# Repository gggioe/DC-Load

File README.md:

Work in progress. At this point, no fully functional board has been produced. Some functional blocks or components have been tested with good results, but since this is a hobby project, there is no ETA. Software and Hardware (even this repo) will be constantly updated. I plan to release a fully functional prototype as soon as possible.

# The Idea
The idea is to build a fully functional instrument that can be easily compared to commercial ones. Commercially available loads are precise, some of them are software-controlled and come with a warranty, however, they tend to not have a high performance/price ratio. Some cheap 30-50 euros Chinese designs are just bad, with very limited specs (generally under 50V, 5A, 100W), and also they tend to use fake or extremely cheap components that fail even at the advertised specs. "Hobbyist" good quality  400 euros loads come with limited specifications like 150V, 20A, and 200W max power. This is ok for general-purpose power supply tests however, nowadays battery tends to have high discharge rates so if you want to test your e-bike battery pack for example, more expensive loads capable of 60-100A, 3-4 kW should be used. Those types of loads however tend to have very high prices>2k and in some cases, you have to be a company to know the exact price. Online exist various more or less good DIY attempts, however, some are a complete joke with specs like 2A, 20V, and 40W max. Don't get me wrong, 20V 2A is perfectly fine for low-power IOT stuff for example, however, nowadays devices tend to get more and more power hungry and power supply more powerful, with a 40w limit even a modern type c phone charger is impossible to fully test. More complex ones are not as precise as i hoped or maybe do not come with an interface that makes it a real bench instrument. Overall all of these projects gave me the impression of being a little "incomplete" and i had a feeling that no one really attempted a commercially competitive DIY solution. At this point, the only thing to do is to build my own DC electronic load that can be used as a real instrument and hopefully be a decent competitor of some commercial solutions, how hard can it be?... right?...

# General design specifications
The main goals are: 

-Good precision: Precise components are cheap these days so since in most cases they outperform more complex discrete designs both in specs and dimension, i will use them without complaining. In general, around 10mA accuracy should be ok for a high power load and for the average hobbyist like me. 

-Good stability: the system should not spontaneously oscillate for example when a too-high/low current is set. Aggressive transient or step can be quite challenging, even if the simulation shows good results, parasitic inductance/capacitance of the real world in components/wiring/trace can cause some instability. What makes the situation worse is that real-world instability/noise can be quite challenging to reproduce in simulation so for now since i do not have the right equipment, i will trust the simulation.

-Safety: The load should remain relatively safe in case of catastrophic failures like reverse polarity or input overvoltage. Due to the moderate-high voltage (maybe up to 500v in later design). Isolation is also a key factor, if an earthed, relatively high voltage source is connected, the user interface like display, button, encoder, pc, etc. should remain isolated. When browsing the internet i noticed that a common flaw that both commercial and non-commercial loads share is the lack of a proper DC-rated transistor, common design even in the 3/400 euro price point tends to use IRF260N (or similar) mosfet, however, if you take a look at the datasheet (safe operating area) they are not even DC rated, this means that DC operation (which is the average operation) is not safe for them. Companies generally compensate by massively underloading them but for me, it is just a bad design. Maybe those transistors were independently tested however in my design i want to use only properly manufactured DC-rated components.

-Modularity: If not too difficult, a modular design is well accepted since it allows to have multiple configurations. Due to the tight demands, if a module ends up being expensive the user who may not need too high specs can build a lower-cost unit and later if necessary add modules to expand the power capability. Of course, if multiple modules in parallel are connected the overall accuracy is reduced because the overall error will be the sum of the error of each module.

-Competitive specs: If i will be not able to achieve at least the same specifications as commercial products there is no point continuing to develop this project since in that case, a worse product will cost me around the same as a commercial well-established one. A good starting point for me is to at least match the commercial product specs so: ≥150V, ≥200W, and since the modular design ≥20A per module should be fine.

-Price: Obviously the cost should remain as low as possible, however, due to my demands an acceptable price will be <100 euros per module. In that case, a complete unit with similar (or even better) specs of commercial loads will end up costing less than the commercial solution.

# Power and Thermal considerations
At now on mouser the best mosfet regarding quality/price ratio is the FDP61N20 however higher power (and more expensive) mosfet such as FDH45N50 can be used, later in the design i will mark some good mid-range alternatives. Due to the relatively small mosfet surface area, in order to get the best performance liquid metal and water cooling system should be used in order to get the best performance. The overall dissipated power strictly depends on the used mosfet, by using a relatively large package transistor with 40x80 water block, liquid metal, and adequate size radiator/pump, 1kW or more (in case of multiple modules in parallel) should be possible. As intuition, heat is the critical part of this project, mosfet has a temperature derating curve that should not be excedeed for safe DC operation, even if a mosfet is 450W max rated for example this will not be true at 50 degree case temperature. Due to the junction-case thermal resistance if the derating curve is not respected even with a relatively low case temperature of around 50 degrees the die will exceed the 150 degree limit thus destroying the transistor. To make things worse each thermal "layer" such as thermal paste, radiator, etc. has its own thermal resistance that adds up to the total mosfet-ambient thermal resistance. At this point i perform some thermal estimation, however, it does not make much sense to upload these numbers since these are just guesses, because to my surprise even large radiator/thermal paste manufacturers do not share the thermal property of their product such as thermal resistance, airflow graph, etc. At this point is unclear to me how without the exact manufacture number the end user should implement a product. It seems like even the pc builder community does not have a clear answer to my problem, and i really don't trust any rule of thumb (like the 120mm x 100W). Now, even if i already know that this is not possible, the only thing that i can do is to experimentally validate each solution starting from the "best", in reality since this will cost me way too much money and time i think that i will use one 80x40 copper (or nickel-plated) water block + Galinstan based thermal compound and then add 120x240 or 120x360mm radiator until i reach decent temperatures.

# Simulation and Waveform
Module Schematic:

1mA Pulsed test:

Even with slightly worse performing op-amps, 1mA is theoretically possible

20A Pulsed test:

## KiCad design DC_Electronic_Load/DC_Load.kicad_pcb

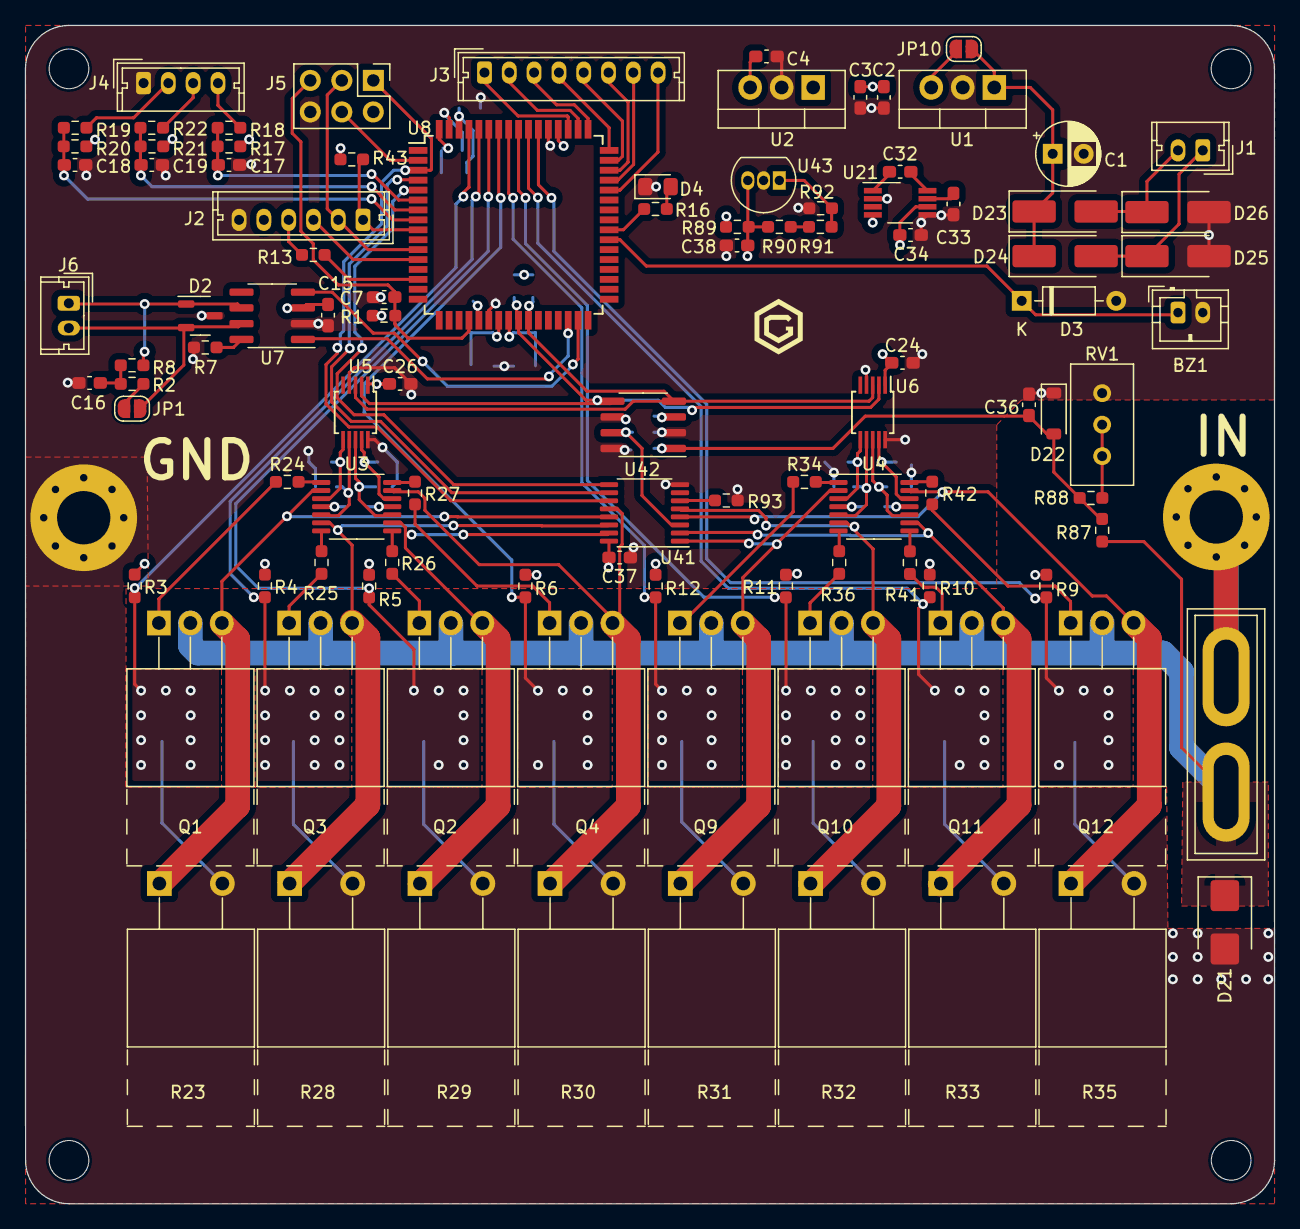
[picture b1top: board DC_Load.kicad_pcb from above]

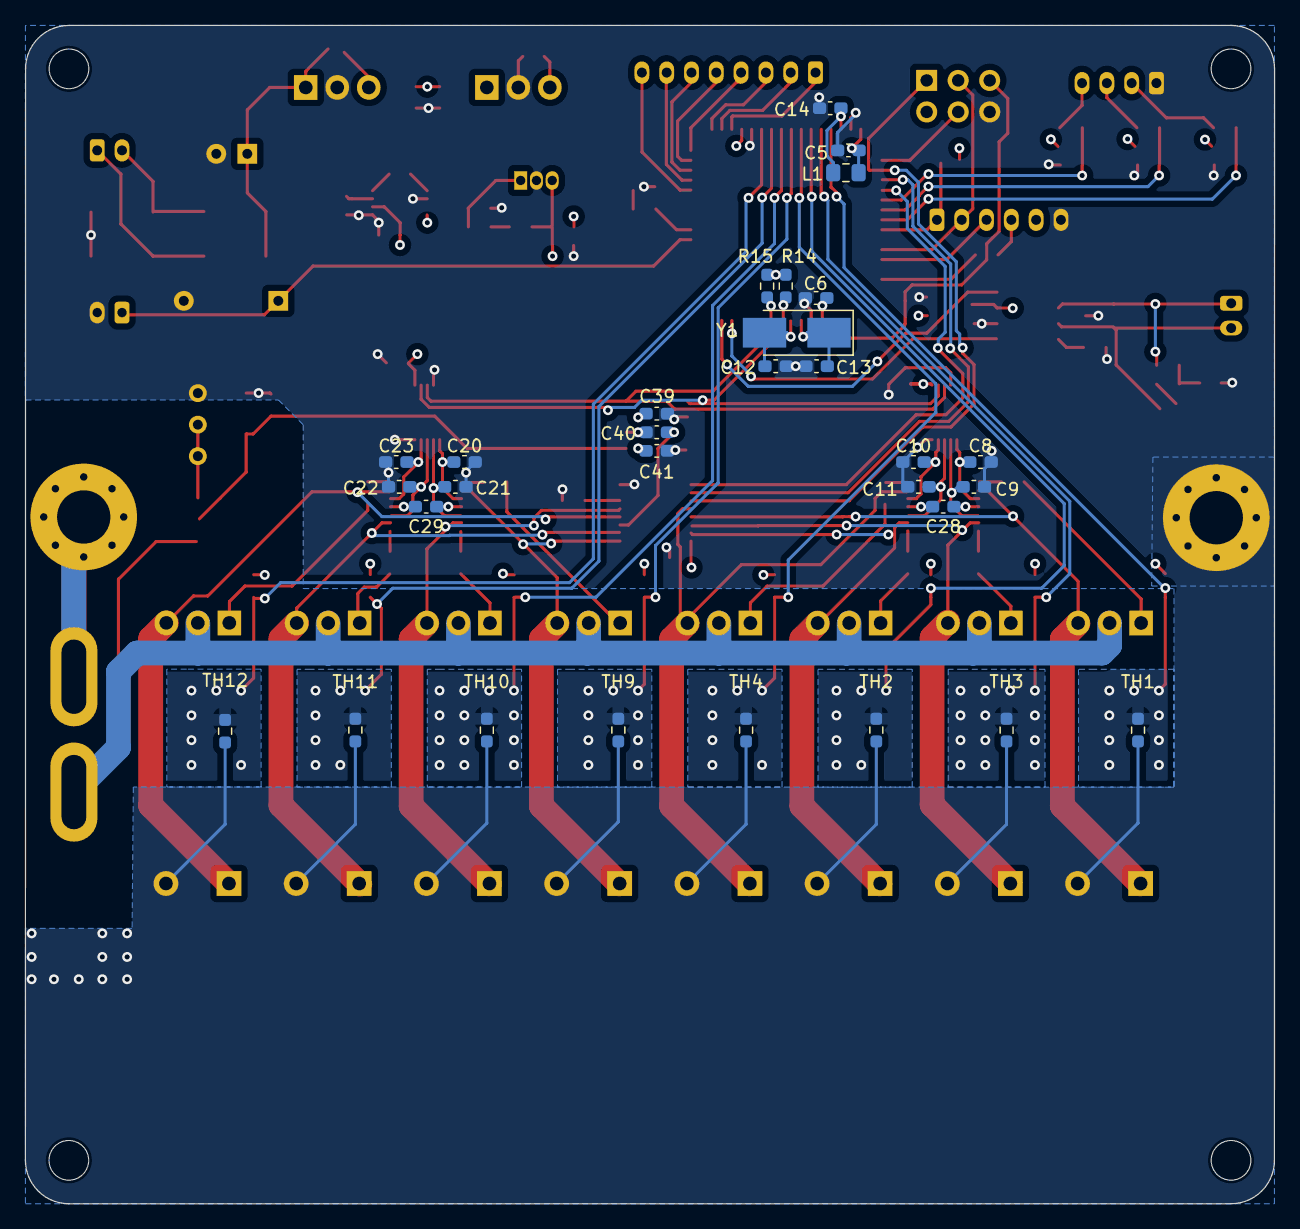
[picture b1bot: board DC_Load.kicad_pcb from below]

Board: 4 copper layers, 100.7 x 95.0 mm, 139 parts (30 on the bottom side), 98 nets.

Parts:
BZ1: Buzzer; JST_PH_B2B-PH-K_1x02_P2.00mm_Vertical
C1: 1000u; CP_Radial_D5.0mm_P2.50mm
C2, C4: 1u; C_0603_1608Metric_Pad1.08x0.95mm_HandSolder
C3, C5, C6, C7, C8, C9, C10, C11, C14, C15, C16, C17, C18, C19, C20, C21, C22, C23, C24, C26, C28, C29, C37, C38, C39: 100n; C_0603_1608Metric_Pad1.08x0.95mm_HandSolder
C12, C13, C36: 22p; C_0603_1608Metric_Pad1.08x0.95mm_HandSolder
C32: 5u; C_0603_1608Metric_Pad1.08x0.95mm_HandSolder
C33, C34: 22u; C_0603_1608Metric_Pad1.08x0.95mm_HandSolder
C40, C41: 1n; C_0603_1608Metric_Pad1.08x0.95mm_HandSolder
D2: PESD2CAN; SOT-23-3
D3: 1N4148; D_DO-35_SOD27_P7.62mm_Horizontal
D4: LED; LED_0805_2012Metric_Pad1.15x1.40mm_HandSolder
D21: SM6T200A; D_SMB
D22: 4.5V; D_SOD-123
D23, D24, D25, D26: SS14; D_SMA_Handsoldering
F1: 50A; Fuse_Blade_ATO_directSolder
H1: PWR+; MountingHole_4.3mm_M4_Pad_Via
H2: PWR-; MountingHole_4.3mm_M4_Pad_Via
H3, H4, H5, H6: MountingHole; MountingHole_3.2mm_M3
J1, J6: Conn_01x02_Pin; Molex_Micro-Latch_53253-0270_1x02_P2.00mm_Vertical
J2: Conn_01x06_Pin; Molex_Micro-Latch_53253-0670_1x06_P2.00mm_Vertical
J3: Conn_01x08_Pin; Molex_Micro-Latch_53253-0870_1x08_P2.00mm_Vertical
J4: Conn_01x04_Pin; Molex_Micro-Latch_53253-0470_1x04_P2.00mm_Vertical
J5: Conn_02x03_Odd_Even; PinHeader_2x03_P2.54mm_Vertical
JP1, JP10: Jumper_2_Open; SolderJumper-2_P1.3mm_Open_RoundedPad1.0x1.5mm
L1: 10uH; L_0805_2012Metric_Pad1.15x1.40mm_HandSolder
Q1, Q2, Q3, Q4, Q9, Q10, Q11, Q12: FDP61N20; TO-220-3_Horizontal_TabUp
R1, R3, R4, R5, R6, R9, R10, R11, R12, R14, R15, R43, R92: 10k; R_0603_1608Metric_Pad0.98x0.95mm_HandSolder
R2, R8, R89: 56; R_0603_1608Metric_Pad0.98x0.95mm_HandSolder
R7, R17, R20, R21: 47k; R_0603_1608Metric_Pad0.98x0.95mm_HandSolder
R13: 220; R_0603_1608Metric_Pad0.98x0.95mm_HandSolder
R16: 330; R_0603_1608Metric_Pad0.98x0.95mm_HandSolder
R18, R19, R22, R93: 1k; R_0603_1608Metric_Pad0.98x0.95mm_HandSolder
R23, R28, R29, R30, R31, R32, R33, R35: 1R; TO-220-2_Horizontal_TabUp
R24, R25, R26, R27, R34, R36, R41, R42: 1.2k; R_0603_1608Metric_Pad0.98x0.95mm_HandSolder
R87: 1M; R_0603_1608Metric_Pad0.98x0.95mm_HandSolder
R88: 22k; R_0603_1608Metric_Pad0.98x0.95mm_HandSolder
R90, R91: 3.6k; R_0603_1608Metric_Pad0.98x0.95mm_HandSolder
RV1: 1k; Potentiometer_Bourns_3296W_Vertical
TH1, TH2, TH3, TH4, TH9, TH10, TH11, TH12: 10k; R_0603_1608Metric_Pad0.98x0.95mm_HandSolder
U1: L7812; TO-220-3_Vertical
U2: L7805; TO-220-3_Vertical
U3, U4: NCS21914; TSSOP-14_4.4x5mm_P0.65mm
U5, U6: MCP4728; MSOP-10_3x3mm_P0.5mm
U7: MCP2551-I-SN; SOIC-8_3.9x4.9mm_P1.27mm
U8: AT90CAN64-16A; TQFP-64_14x14mm_P0.8mm
U9: Gio_5x5
U21: LM7705; VSSOP-8_3.0x3.0mm_P0.65mm
U41: XS3A4051PWJ; TSSOP-16_4.4x5mm_P0.65mm
U42: MCP3422; SOIC-8_3.9x4.9mm_P1.27mm
U43: TL431LP; TO-92_Inline
Y1: Crystal; Crystal_SMD_5032-2Pin_5.0x3.2mm_HandSoldering

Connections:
+4V: C37.1, C38.1, R89.2, R90.1, U41.16 (VCC), U43.3 (K)
+5V: C4.1, C6.1, C14.1, C15.1, C24.1, C26.1, C39.1, J2.5, J5.2, L1.1, R1.1, R3.1, R4.1, R5.1, R6.1, R9.1, R10.1, R11.1, R12.1, R14.1, R15.2, R17.1, R20.1, R21.1, R43.2, R89.1, U2.3 (OUT), U5.1 (VDD), U6.1 (VDD), U7.3 (VDD), U8.21 (VCC), U8.52 (VCC), U8.62 (AREF), U21.4 (VDD), U42.3 (Vdd)
+12V: C2.1, C3.1, C28.1, C29.1, JP10.2 (B), U1.3 (OUT), U2.1 (IN), U3.4 (V+), U4.4 (V+)
-VSW: C28.2, C29.2, C34.1, U3.11 (V-), U4.11 (V-), U21.6 (VOUT)
B1: J5.1, U8.3 (PE1), U41.11 (S1)
B2: U8.4 (PE2), U41.10 (S2)
B3: U8.5 (PE3), U41.9 (S3)
BCKL_CTRL: R13.2, U8.14 (PB4)
BZ: BZ1.1 (-), D3.1 (K), U8.39 (PC4)
C1: J3.5, U8.47 (PA4)
C2: J3.6, U8.46 (PA5)
C3: J3.7, U8.45 (PA6)
C4: J3.8, U8.44 (PA7)
CAN_RX: U7.4 (RXD), U8.31 (PD6)
CAN_TX: U7.1 (TXD), U8.30 (PD5)
CH1: C8.1, U3.3 (+), U5.6 (VOUTA)
CH2: C9.1, U3.5 (+), U5.7 (VOUTB)
CH3: C11.1, U3.10 (+), U5.8 (VOUTC)
CH4: C10.1, U3.12 (+), U5.9 (VOUTD)
CH5: C20.1, U4.3 (+), U6.6 (VOUTA)
CH6: C21.1, U4.5 (+), U6.7 (VOUTB)
CH7: C22.1, U4.10 (+), U6.8 (VOUTC)
CH8: C23.1, U4.12 (+), U6.9 (VOUTD)
CS: J2.1, R43.1, U8.9 (PE7)
E: J5.4, U8.2 (PE0)
EN1: C17.1, R17.2, R18.1, U8.6 (PE4)
EN2: C19.1, R21.2, R22.1, U8.7 (PE5)
GND: BZ1.2 (+), C1.2, C2.2, C3.2, C4.2, C5.2, C6.2, C7.2, C8.2, C9.2, C10.2, C11.2, C12.2, C13.2, C14.2, C15.2, C16.2, C17.2, C18.2, C19.2, C20.2, C21.2, C22.2, C23.2, C24.2, C26.2, C33.2, C34.2, C36.2, C37.2, C38.2, C39.2, C40.2, C41.2, D2.3 (common), D3.2 (A), D4.1 (K), D21.2 (A2), D22.1 (A1), D25.2 (A), D26.2 (A), H2.1, J2.6, J4.1, J5.6, R7.1, R23.2, R28.2, R29.2, R30.2, R31.2, R32.2, R33.2, R35.2, R92.2, R93.1, RV1.3, TH1.2, TH2.2, TH3.2, TH4.2, TH9.2, TH10.2, TH11.2, TH12.2, U1.2 (GND), U2.2 (GND), U5.4 (~LDAC), U5.10 (VSS), U6.4 (~LDAC), U6.10 (VSS), U7.2 (VSS), U8.22 (GND), U8.53 (GND), U8.63 (AGND), U21.2 (GND), U21.5 (GND), U41.8 (GND), U42.2 (CH1-), U42.6 (Vss), U42.8 (CH2-), U43.2 (A)
I1: Q1.3 (S), R23.1, U3.2 (-), U41.13 (Y0)
I2: Q3.3 (S), R28.1, U3.6 (-), U41.14 (Y1)
I3: Q2.3 (S), R29.1, U3.9 (-), U41.15 (Y2)
I4: Q4.3 (S), R30.1, U3.13 (-), U41.12 (Y3)
I5: Q9.3 (S), R31.1, U4.2 (-), U41.1 (Y4)
I6: Q10.3 (S), R32.1, U4.6 (-), U41.5 (Y5)
I7: Q11.3 (S), R33.1, U4.9 (-), U41.2 (Y6)
I8: Q12.3 (S), R35.1, U4.13 (-), U41.4 (Y7)
IMP: C40.1, U41.3 (Z), U42.7 (CH2+)
IN: D21.1 (A1), F1.1, Q1.2 (D), Q2.2 (D), Q3.2 (D), Q4.2 (D), Q9.2 (D), Q10.2 (D), Q11.2 (D), Q12.2 (D), R87.2
MOSI: J2.3, U8.12 (PB2)
unnamed: C16.1, R2.1, R8.2
unnamed: D2.1 (A1), J6.1, R8.1, U7.6 (CANL)
unnamed: D2.2 (A2), J6.2, JP1.1 (A), U7.7 (CANH)
unnamed: D4.2 (A), R16.2
unnamed: D23.2 (A), D26.1 (K), J1.2
unnamed: D24.2 (A), D25.1 (K), J1.1
unnamed: F1.2, H1.1
unnamed: J2.4, R13.1
unnamed: J4.2, R19.2
unnamed: J4.3, R22.2
unnamed: J4.4, R18.2
unnamed: JP1.2 (B), R2.2
unnamed: Q1.1 (G), R24.2
unnamed: Q2.1 (G), R26.2
unnamed: Q3.1 (G), R25.2
unnamed: Q4.1 (G), R27.2
unnamed: Q9.1 (G), R34.2
unnamed: Q10.1 (G), R36.2
unnamed: Q11.1 (G), R41.2
unnamed: Q12.1 (G), R42.2
unnamed: R24.1, U3.1
unnamed: R25.1, U3.7
unnamed: R26.1, U3.8
unnamed: R27.1, U3.14
unnamed: R34.1, U4.1
unnamed: R36.1, U4.7
unnamed: R41.1, U4.8
unnamed: R42.1, U4.14
unnamed: R88.2, RV1.1, RV1.2
unnamed: R90.2, R91.1
unnamed: R7.2, U7.8 (Rs)
unnamed: C5.1, L1.2, U8.64 (AVCC)
unnamed: C12.1, U8.24 (XTAL1), Y1.2
unnamed: C13.1, U8.23 (XTAL2), Y1.1
unnamed: C32.1, U21.1 (CF+)
unnamed: C32.2, U21.8 (CF-)
unnamed: C33.1, U21.7 (CRES)
unnamed: R93.2, U41.6 (E)
unnamed: R91.2, R92.1, U43.1 (REF)
OUT_ON: R16.1, U8.40 (PC5)
R1: J3.1, U8.51 (PA0)
R2: J3.2, U8.50 (PA1)
R3: J3.3, U8.49 (PA2)
R4: J3.4, U8.48 (PA3)
RST: C7.1, J5.5, R1.2, U8.20 (~RESET)
SCK: J2.2, J5.3, U8.11 (PB1)
SCL: R14.2, U5.2 (SCL), U6.2 (SCL), U8.25 (PD0), U42.5 (SCL)
SDA: R15.1, U5.3 (SDA), U6.3 (SDA), U8.26 (PD1), U42.4 (SDA)
SW: C18.1, R19.1, R20.2, U8.8 (PE6)
TM1: R3.2, TH1.1, U8.61 (PF0)
TM2: R4.2, TH3.1, U8.60 (PF1)
TM3: R5.2, TH2.1, U8.59 (PF2)
TM4: R6.2, TH4.1, U8.58 (PF3)
TM5: R12.2, TH9.1, U8.57 (PF4)
TM6: R11.2, TH10.1, U8.56 (PF5)
TM7: R10.2, TH11.1, U8.55 (PF6)
TM8: R9.2, TH12.1, U8.54 (PF7)
VCC: C1.1, D23.1 (K), D24.1 (K), JP10.1 (A), U1.1 (IN)
VMP: C36.1, C41.1, D22.2 (A2), R87.1, R88.1, U42.1 (CH1+)

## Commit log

2024-01-01 Updated 4 layer test board
2025-01-21 Create folder
2025-01-21 Cleanup
